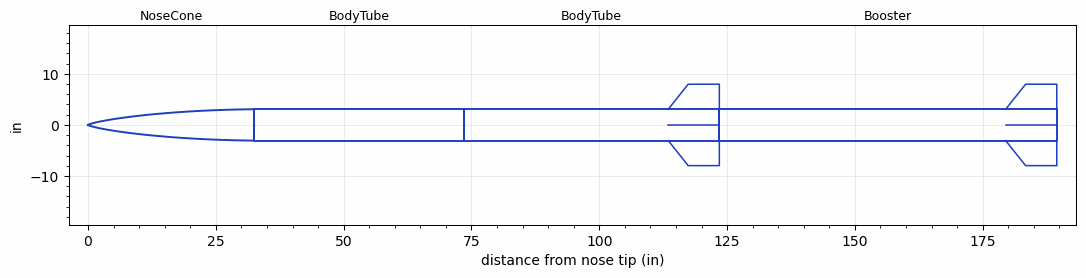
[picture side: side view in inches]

<RASAeroDocument>
 <FileVersion>2</FileVersion>
 <RocketDesign>
  <NoseCone>
   <Length>32.48</Length>
   <Diameter>6.12</Diameter>
   <Shape>LV-Haack</Shape>
   <Location>0</Location>
  </NoseCone>
  <BodyTube>
   <Length>41</Length>
   <Diameter>6.12</Diameter>
   <Location>32.48</Location>
  </BodyTube>
  <BodyTube>
   <Length>50</Length>
   <Diameter>6.12</Diameter>
   <Location>73.48</Location>
   <Fin>
    <Count>4</Count>
    <Chord>10</Chord>
    <Span>4.9</Span>
    <SweepDistance>3.9</SweepDistance>
    <TipChord>6.1</TipChord>
    <Thickness>0.188</Thickness>
    <Location>10</Location>
    <AirfoilSection>Rounded</AirfoilSection>
   </Fin>
  </BodyTube>
  <Booster>
   <Length>66</Length>
   <Diameter>6.12</Diameter>
   <InsideDiameter>6.12</InsideDiameter>
   <Location>123.48</Location>
   <ShoulderLength>0</ShoulderLength>
   <Fin>
    <Count>4</Count>
    <Chord>10</Chord>
    <Span>4.9</Span>
    <SweepDistance>3.9</SweepDistance>
    <TipChord>6.1</TipChord>
    <Thickness>0.188</Thickness>
    <Location>10</Location>
    <AirfoilSection>Rounded</AirfoilSection>
   </Fin>
  </Booster>
  <Surface>Rough Camouflage Paint</Surface>
  <ModifiedBarrowman>True</ModifiedBarrowman>
  <Turbulence>False</Turbulence>
  <UseBooster1>False</UseBooster1>
  <UseBooster2>False</UseBooster2>
 </RocketDesign>
 <LaunchSite>
  <Altitude>2782</Altitude>
  <Pressure>29.9</Pressure>
  <RodAngle>3</RodAngle>
  <RodLength>35</RodLength>
  <Temperature>95</Temperature>
  <WindSpeed>4.47</WindSpeed>
 </LaunchSite>
 <Recovery>
  <Altitude1>0</Altitude1>
  <Altitude2>0</Altitude2>
  <DeviceType1>None</DeviceType1>
  <DeviceType2>None</DeviceType2>
  <Event1>False</Event1>
  <Event2>False</Event2>
  <Size1>0</Size1>
  <Size2>0</Size2>
  <EventType1>None</EventType1>
  <EventType2>None</EventType2>
  <CD1>0</CD1>
  <CD2>0</CD2>
 </Recovery>
 <SimulationList>
  <Simulation>
   <SustainerEngine>N2847  (SustainerTest)</SustainerEngine>
   <SustainerLaunchWt>82.3</SustainerLaunchWt>
   <SustainerNozzleDiameter>2.7</SustainerNozzleDiameter>
   <SustainerCG>77.91</SustainerCG>
   <SustainerIgnitionDelay>3</SustainerIgnitionDelay>
   <Booster1Engine>O4185  (BoosterTest)</Booster1Engine>
   <Booster1LaunchWt>183</Booster1LaunchWt>
   <Booster1SeparationDelay>0.5</Booster1SeparationDelay>
   <Booster1IgnitionDelay>0</Booster1IgnitionDelay>
   <Booster1CG>126</Booster1CG>
   <Booster1NozzleDiameter>3.5</Booster1NozzleDiameter>
   <IncludeBooster1>True</IncludeBooster1>
   <Booster2Delay>0</Booster2Delay>
   <IncludeBooster2>False</IncludeBooster2>
   <TimetoApogee>52.22853</TimetoApogee>
   <MaxAltitude>38663.02</MaxAltitude>
   <MaxVelocity>1867.531</MaxVelocity>
  </Simulation>
 </SimulationList>
</RASAeroDocument>
